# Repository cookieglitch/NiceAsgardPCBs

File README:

The Nice Asgard Project - Ultimate Road Test (element14/Texas Instruments)

PCB files produced in EAGLE

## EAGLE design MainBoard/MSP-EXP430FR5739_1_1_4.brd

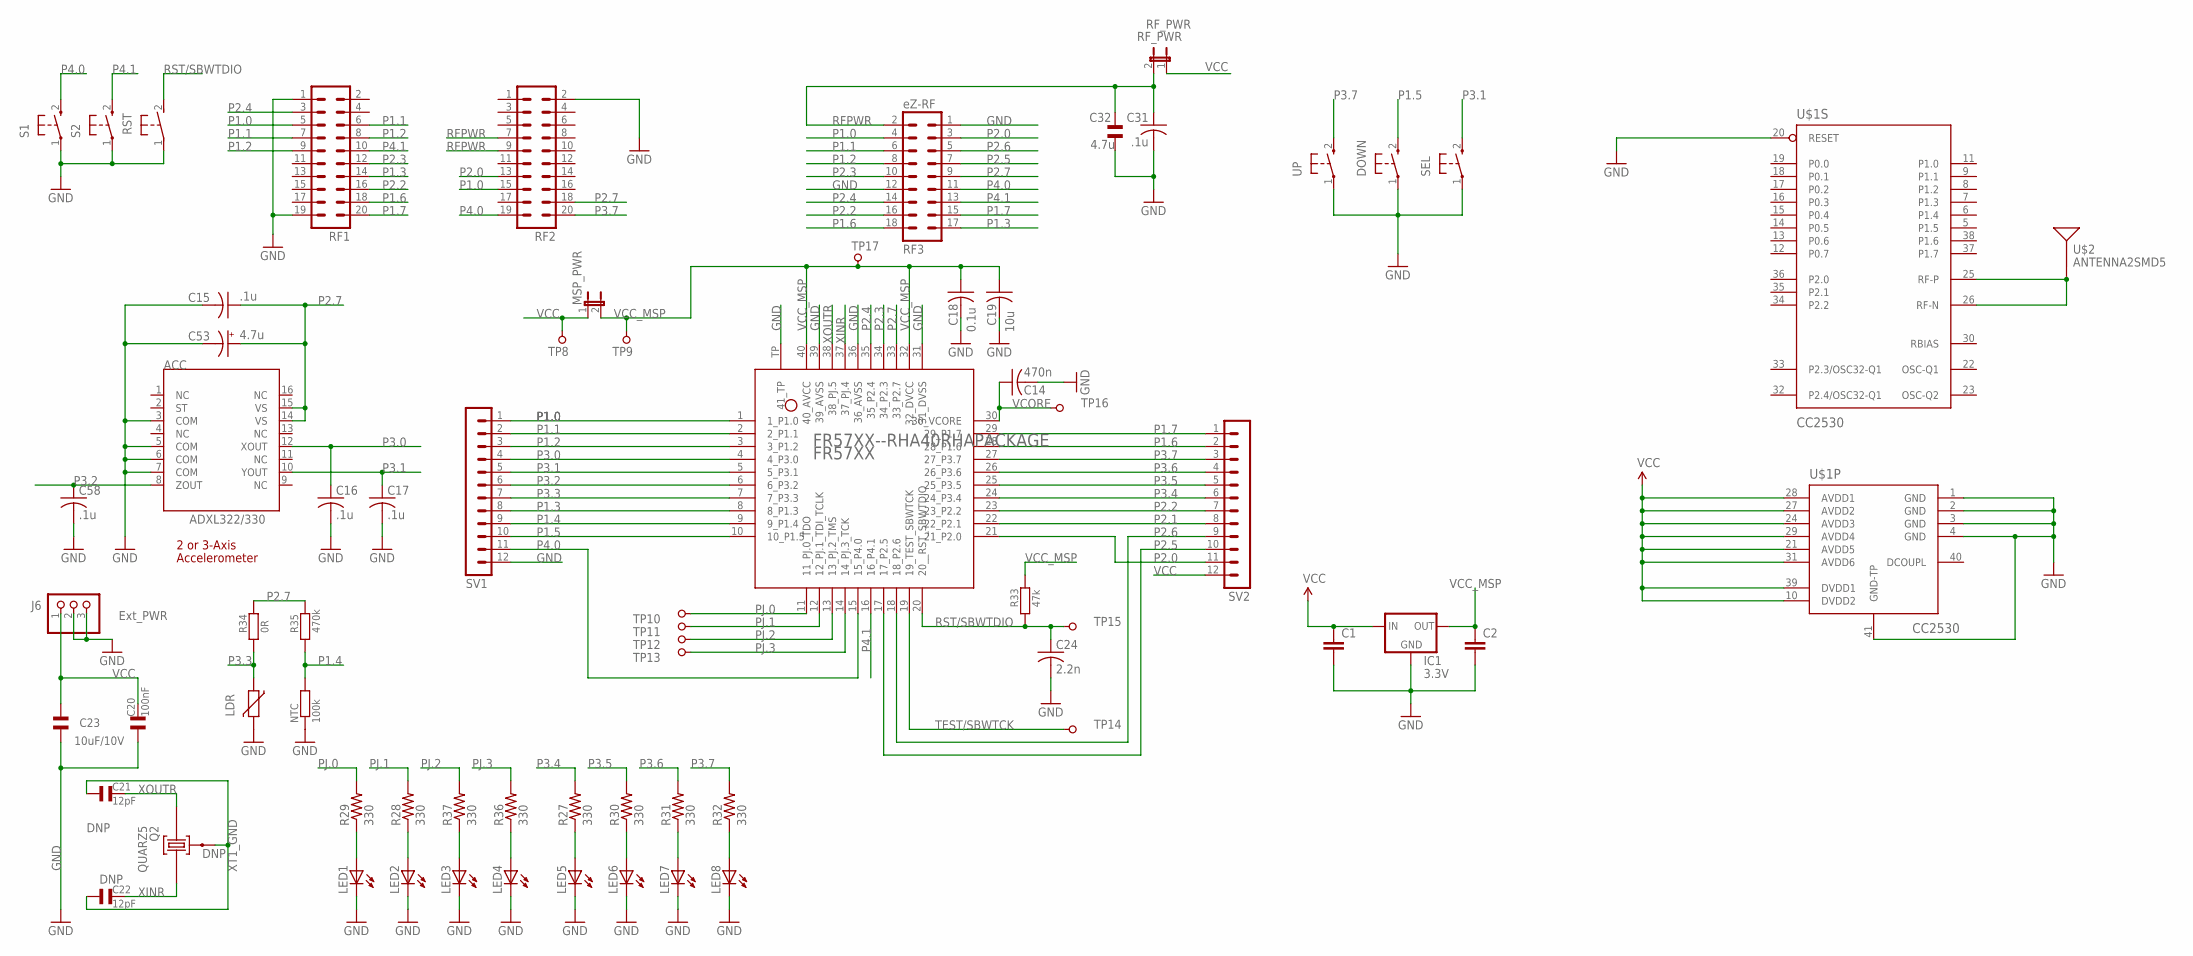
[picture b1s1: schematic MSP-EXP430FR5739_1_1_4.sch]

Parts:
ACC: ADXL322/330; RSA16
C1, C2: CAPPTH1; CAP-PTH-5MM
C14: 470n; C0603
C15, C16, C17, C31, C58: .1u; C0603
C18: 0.1u; C0603
C19: 10u; C0603
C20: 100nF; 0603
C21, C22: 12pF; 0603
C23: 10uF/10V; 0805
C24: 2.2n; C0603
C32: 4.7u; CSMD0805
C53: 4.7u; SMC_A
DOWN: PB; PBTH
FR57XX: FR57XX--RHA40RHAPACKAGE; RHA40
IC1: 3.3V; 78LXX
J6: 1X03
LDR: R3,4; R-3,4
LED1, LED2, LED3, LED4, LED5, LED6, LED7, LED8: LEDCHIPLED_0603; CHIPLED_0603
MSP_PWR: JP1E; JP1
NTC: 100k; 0805
Q2: QUARZ5
R27, R28, R29, R30, R31, R32, R36, R37: 330; R0603
R33: 47k; 0603
R34: 0R; 0603
R35: 470k; 0603
RF1, RF2: TFM-110-02-SM-D-A-K
RF3: eZ-RF; MA09-2
RF_PWR: RF_PWR; JP1
RST: EVQPPDASTD; EVQPPDA
S1, S2: PB; PBTH
SEL: PB; PBTH
SV1, SV2: MA12-1
TP8, TP9, TP10, TP11, TP12, TP13, TP14, TP15, TP16, TP17: TP05TP10; TP10
U$1: CC2530; QFN50P600X600X100-41N
U$2: ANTENNA2SMD5; ANTENNA-CHIP5
UP: PB; PBTH

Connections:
DCOUPL: U$1.40 (DCOUPL)
GND: ACC.3 (COM), ACC.5 (COM), ACC.6 (COM), ACC.7 (COM), C1.2, C2.2, C14.2, C15.2, C16.2, C17.2, C18.2, C19.2, C20.1, C23.1, C24.2, C31.2, C32.2, C53.-, C58.2, DOWN.1, FR57XX.31 (31_DVSS), FR57XX.36 (36_AVSS), FR57XX.39 (39_AVSS), FR57XX.TP (41_TP), IC1.GND, J6.2, J6.3, LDR.2, LED1.C, LED2.C, LED3.C, LED4.C, LED5.C, LED6.C, LED7.C, LED8.C, NTC.1, RF1.1, RF1.19, RF2.2, RF3.1, RF3.12, RST.1, S1.1, S2.1, SEL.1, SV1.12, U$1.1 (GND), U$1.2 (GND), U$1.3 (GND), U$1.4 (GND), U$1.20 (RESET), U$1.41 (GND-TP), UP.1
unnamed: U$1.25 (RF-P), U$1.26 (RF-N), U$2.FEED
unnamed: LED6.A, R30.1
unnamed: LED7.A, R31.1
unnamed: LED5.A, R27.1
unnamed: LED8.A, R32.1
unnamed: LED2.A, R28.1
unnamed: LED1.A, R29.1
unnamed: LED4.A, R36.1
unnamed: LED3.A, R37.1
P1.0: FR57XX.1 (1_P1.0), RF1.5, RF2.15, RF3.4, SV1.1
P1.1: FR57XX.2 (2_P1.1), RF1.6, RF1.7, RF3.6, SV1.2
P1.2: FR57XX.3 (3_P1.2), RF1.8, RF1.9, RF3.8, SV1.3
P1.3: FR57XX.8 (8_P1.3), RF1.14, RF3.17, SV1.8
P1.4: FR57XX.9 (9_P1.4), NTC.2, R35.1, SV1.9
P1.5: DOWN.2 (S), FR57XX.10 (10_P1.5), SV1.10
P1.6: FR57XX.28 (28_P1.6), RF1.18, RF3.18, SV2.2
P1.7: FR57XX.29 (29_P1.7), RF1.20, RF3.15, SV2.1
P2.0: FR57XX.21 (21_P2.0), RF2.13, RF3.3, SV2.11
P2.1: FR57XX.22 (22_P2.1), SV2.8
P2.2: FR57XX.23 (23_P2.2), RF1.16, RF3.16, SV2.7
P2.3: FR57XX.34 (34_P2.3), RF1.12, RF3.10
P2.4: FR57XX.35 (35_P2.4), RF1.3, RF3.14
P2.5: FR57XX.17 (17_P2.5), RF3.7, SV2.10
P2.6: FR57XX.18 (18_P2.6), RF3.5, SV2.9
P2.7: ACC.14 (VS), ACC.15 (VS), C15.1, C53.+, FR57XX.33 (33_P2.7), R34.2, R35.2, RF2.18, RF3.9
P3.0: ACC.12 (XOUT), C16.1, FR57XX.4 (4_P3.0), SV1.4
P3.1: ACC.10 (YOUT), C17.1, FR57XX.5 (5_P3.1), SEL.2 (S), SV1.5
P3.2: ACC.8 (ZOUT), C58.1, FR57XX.6 (6_P3.2), SV1.6
P3.3: FR57XX.7 (7_P3.3), LDR.1, R34.1, SV1.7
P3.4: FR57XX.24 (24_P3.4), R27.2, SV2.6
P3.5: FR57XX.25 (25_P3.5), R30.2, SV2.5
P3.6: FR57XX.26 (26_P3.6), R31.2, SV2.4
P3.7: FR57XX.27 (27_P3.7), R32.2, RF2.20, SV2.3, UP.2 (S)
P4.0: FR57XX.15 (15_P4.0), RF2.19, RF3.11, S1.2 (S), SV1.11
P4.1: FR57XX.16 (16_P4.1), RF1.10, RF3.13, S2.2 (S)
PJ.0: FR57XX.11 (11_PJ.0_TDO), R29.2, TP10.1
PJ.1: FR57XX.12 (12_PJ.1_TDI_TCLK), R28.2, TP11.1
PJ.2: FR57XX.13 (13_PJ.2_TMS), R37.2, TP12.1
PJ.3: FR57XX.14 (14_PJ.3_TCK), R36.2, TP13.1
RFPWR: C31.1, C32.1, RF2.7, RF2.9, RF3.2, RF_PWR.2
RST/SBWTDIO: C24.1, FR57XX.20 (20__RST_SBWTDIO), R33.1, RST.2 (S), TP15.1
TEST/SBWTCK: FR57XX.19 (19_TEST_SBWTCK), TP14.1
VCC: C1.1, C20.2, C23.2, IC1.IN, J6.1, MSP_PWR.1, RF_PWR.1, SV2.12, TP8.1, U$1.10 (DVDD2), U$1.21 (AVDD5), U$1.24 (AVDD3), U$1.27 (AVDD2), U$1.28 (AVDD1), U$1.29 (AVDD4), U$1.31 (AVDD6), U$1.39 (DVDD1)
VCC_MSP: C2.1, C18.1, C19.1, FR57XX.32 (32_DVCC), FR57XX.40 (40_AVCC), IC1.OUT, MSP_PWR.2, R33.2, TP9.1, TP17.1
VCORE: C14.1, FR57XX.30 (30_VCORE), TP16.1
XINR: C22.2, FR57XX.37 (37_PJ.4), Q2.1
XOUTR: C21.2, FR57XX.38 (38_PJ.5), Q2.2
XT1_GND: C21.1, C22.1, Q2.GND@0 (0)

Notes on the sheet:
Ext_PWR
DNP
2 or 3-Axis
Accelerometer

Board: 2 copper layers, 68 parts (0 on the bottom side), 49 nets, no tracks yet.

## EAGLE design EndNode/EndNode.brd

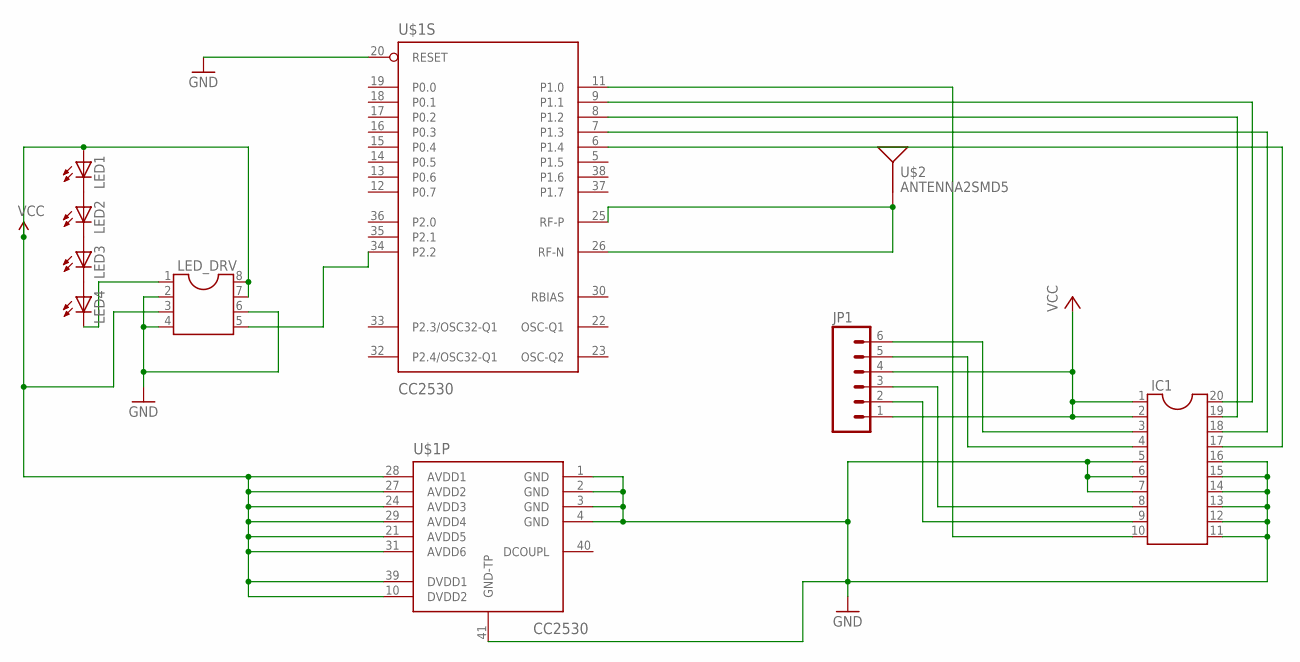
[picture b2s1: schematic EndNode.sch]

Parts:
IC1: DIL20
JP1: M06POLAR; MOLEX-1X6
LED1, LED2, LED3, LED4: LED5MM
LED_DRV: DIL8; DIL08
U$1: CC2530; QFN50P600X600X100-41N
U$2: ANTENNA2SMD5; ANTENNA-CHIP5

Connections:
DCOUPL: U$1.40 (DCOUPL)
GND: IC1.5, IC1.6, IC1.7, IC1.11, IC1.12, IC1.13, IC1.14, IC1.15, IC1.16, LED_DRV.2, LED_DRV.4, LED_DRV.6, U$1.1 (GND), U$1.2 (GND), U$1.3 (GND), U$1.4 (GND), U$1.20 (RESET), U$1.41 (GND-TP)
unnamed: LED1.K (C), LED2.A
unnamed: LED2.K (C), LED3.A
unnamed: LED3.K (C), LED4.A
unnamed: LED4.K (C), LED_DRV.1
unnamed: IC1.3, JP1.6
unnamed: IC1.10, U$1.11 (P1.0)
unnamed: LED_DRV.5, U$1.34 (P2.2)
unnamed: IC1.20, U$1.9 (P1.1)
unnamed: IC1.19, U$1.8 (P1.2)
unnamed: IC1.18, U$1.7 (P1.3)
unnamed: IC1.17, U$1.6 (P1.4)
unnamed: IC1.4, JP1.5
unnamed: IC1.8, JP1.3
unnamed: IC1.9, JP1.2
U$2: U$1.25 (RF-P), U$1.26 (RF-N), U$2.FEED
VCC: LED1.A, LED_DRV.3, LED_DRV.7, LED_DRV.8, U$1.10 (DVDD2), U$1.21 (AVDD5), U$1.24 (AVDD3), U$1.27 (AVDD2), U$1.28 (AVDD1), U$1.29 (AVDD4), U$1.31 (AVDD6), U$1.39 (DVDD1)
VM: IC1.1, IC1.2, JP1.1, JP1.4

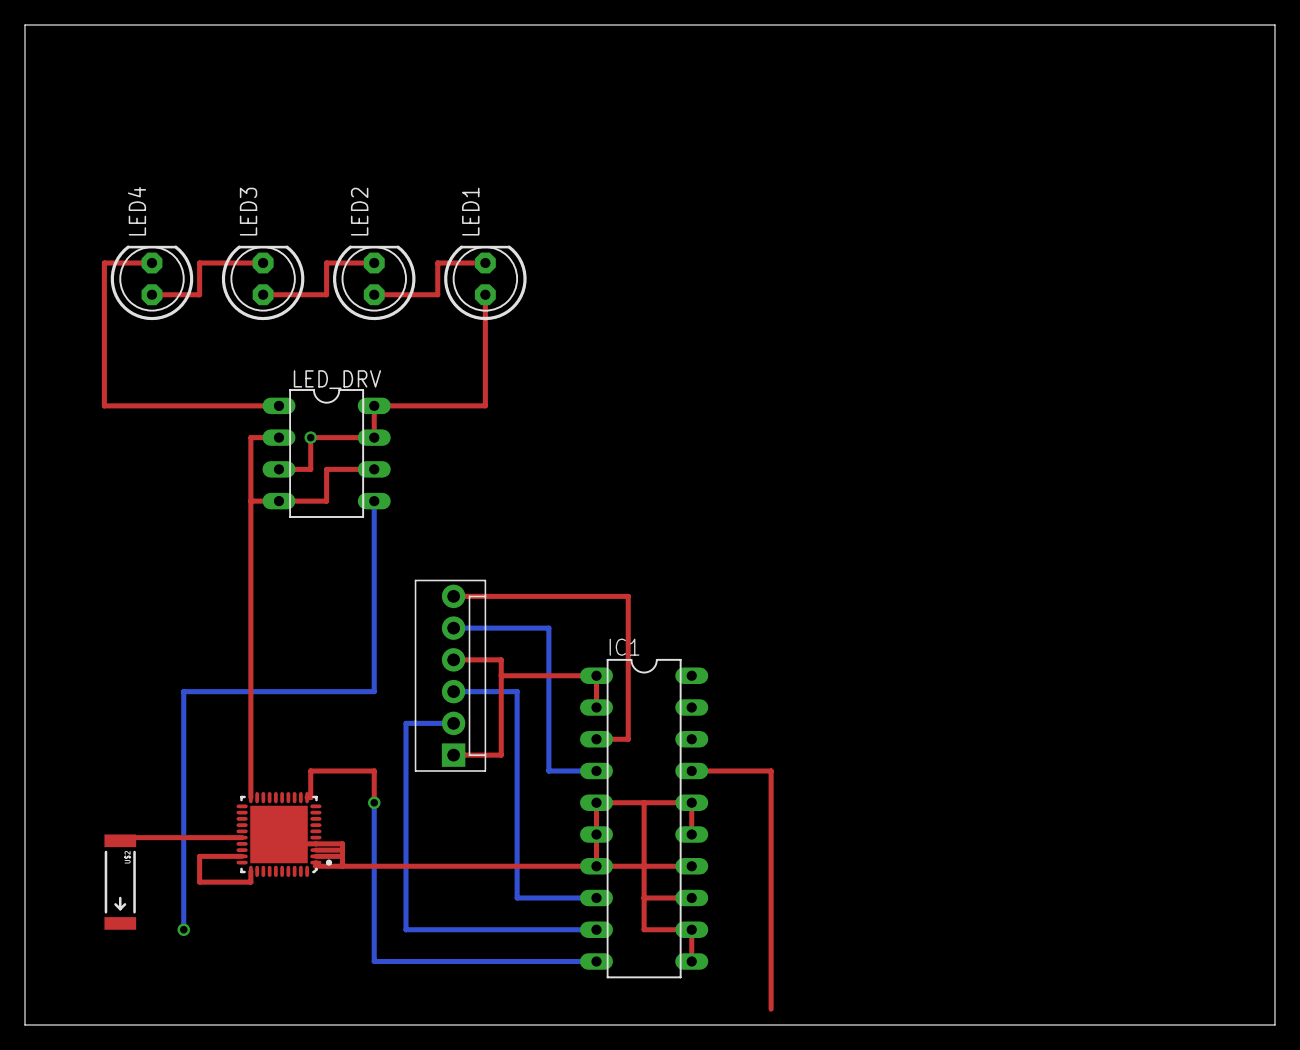
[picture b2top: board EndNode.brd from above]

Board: 2 copper layers, 100.0 x 80.0 mm, 9 parts (0 on the bottom side), 18 nets.

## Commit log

2012-06-24 move to PCB layout. Route some components

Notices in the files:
parts and their libraries:
SparkFun-RF: Licensing: CC v3.0 Share-Alike You are welcome to use this library for commercial purposes.
